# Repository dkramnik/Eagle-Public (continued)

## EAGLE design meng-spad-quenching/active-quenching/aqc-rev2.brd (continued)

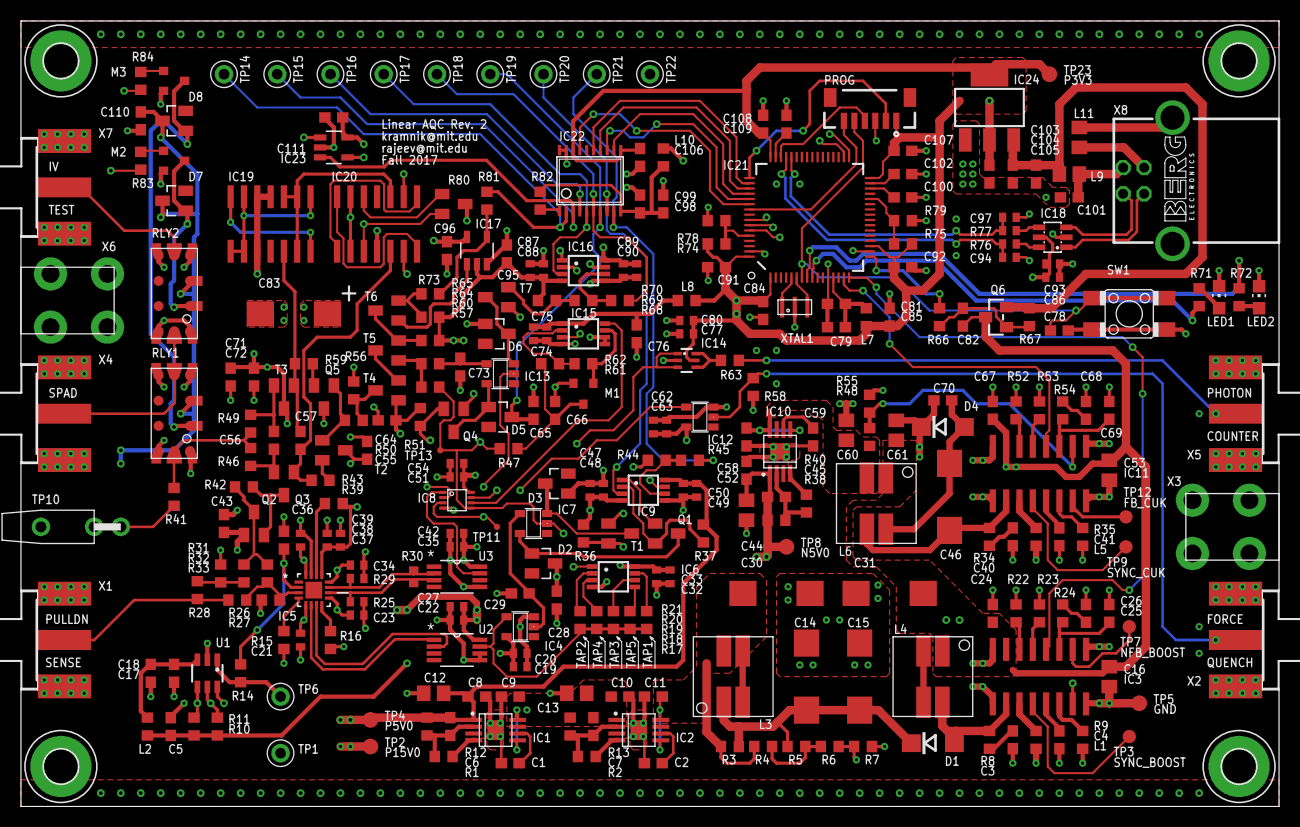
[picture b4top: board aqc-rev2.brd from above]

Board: 4 copper layers, 120.0 x 74.9 mm, 299 parts (0 on the bottom side), 171 nets.

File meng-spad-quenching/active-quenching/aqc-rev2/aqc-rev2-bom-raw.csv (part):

"Part";"Value";"Device";"Package";"Description";"";
"C1";"10n";"C-EUC0603";"C0603";"CAPACITOR, European symbol";"";
"C2";"10n";"C-EUC0603";"C0603";"CAPACITOR, European symbol";"";
"C3";"1n";"C-EUC0603";"C0603";"CAPACITOR, European symbol";"";
"C4";"1300p";"C-EUC0603";"C0603";"CAPACITOR, European symbol";"";
"C5";"100n";"C-EUC0603";"C0603";"CAPACITOR, European symbol";"";
"C6";"10n";"C-EUC0603";"C0603";"CAPACITOR, European symbol";"";
"C7";"10n";"C-EUC0603";"C0603";"CAPACITOR, European symbol";"";
"C8";"100n";"C-EUC0603";"C0603";"CAPACITOR, European symbol";"";
"C9";"100n";"C-EUC0603";"C0603";"CAPACITOR, European symbol";"";
"C10";"100n";"C-EUC0603";"C0603";"CAPACITOR, European symbol";"";
"C11";"100n";"C-EUC0603";"C0603";"CAPACITOR, European symbol";"";
"C12";"10u";"C-EUC0805";"C0805";"CAPACITOR, European symbol";"";
"C13";"10u";"C-EUC0805";"C0805";"CAPACITOR, European symbol";"";
"C14";"47u, 20V";"CPOL-EUCT7343";"CT7343";"POLARIZED CAPACITOR, European symbol";"";
"C15";"47u, 20V";"CPOL-EUCT7343";"CT7343";"POLARIZED CAPACITOR, European symbol";"";
"C16";"4.7u";"C-EUC0805";"C0805";"CAPACITOR, European symbol";"";
"C17";"4u7";"C-EUC0603";"C0603";"CAPACITOR, European symbol";"";
"C18";"100n";"C-EUC0603";"C0603";"CAPACITOR, European symbol";"";
"C19";"100n";"C-EUC0402";"C0402";"CAPACITOR, European symbol";"";
"C20";"10n";"C-EUC0402";"C0402";"CAPACITOR, European symbol";"";
"C21";"10n";"C-EUC0402";"C0402";"CAPACITOR, European symbol";"";
"C22";"10n";"C-EUC0402";"C0402";"CAPACITOR, European symbol";"";
"C23";"10n";"C-EUC0402";"C0402";"CAPACITOR, European symbol";"";
"C24";"100n";"C-EUC0603";"C0603";"CAPACITOR, European symbol";"";
"C25";"15n";"C-EUC0603";"C0603";"CAPACITOR, European symbol";"";
"C26";"220p";"C-EUC0603";"C0603";"CAPACITOR, European symbol";"";
"C27";"100n";"C-EUC0402";"C0402";"CAPACITOR, European symbol";"";
"C28";"470p";"C-EUC0603";"C0603";"CAPACITOR, European symbol";"";
"C29";"10p";"C-EUC0603";"C0603";"CAPACITOR, European symbol";"";
"C30";"47u, 20V";"CPOL-EUCT7343";"CT7343";"POLARIZED CAPACITOR, European symbol";"";
"C31";"47u, 20V";"CPOL-EUCT7343";"CT7343";"POLARIZED CAPACITOR, European symbol";"";
"C32";"100n";"C-EUC0402";"C0402";"CAPACITOR, European symbol";"";
"C33";"10n";"C-EUC0402";"C0402";"CAPACITOR, European symbol";"";
"C34";"100n";"C-EUC0402";"C0402";"CAPACITOR, European symbol";"";
"C35";"100n";"C-EUC0402";"C0402";"CAPACITOR, European symbol";"";
"C36";"1n";"C-EUC0603";"C0603";"CAPACITOR, European symbol";"";
"C37";"100n";"C-EUC0402";"C0402";"CAPACITOR, European symbol";"";
"C38";"100n";"C-EUC0402";"C0402";"CAPACITOR, European symbol";"";
"C39";"10n";"C-EUC0402";"C0402";"CAPACITOR, European symbol";"";
"C40";"10n";"C-EUC0603";"C0603";"CAPACITOR, European symbol";"";
"C41";"1300p";"C-EUC0603";"C0603";"CAPACITOR, European symbol";"";
"C42";"10n";"C-EUC0402";"C0402";"CAPACITOR, European symbol";"";
"C43";"100n";"C-EUC0603";"C0603";"CAPACITOR, European symbol";"";
"C44";"10u";"C-EUC0805";"C0805";"CAPACITOR, European symbol";"";
"C45";"10n";"C-EUC0603";"C0603";"CAPACITOR, European symbol";"";
"C46";"68u, 16V";"CPOL-EUCT7343";"CT7343";"POLARIZED CAPACITOR, European symbol";"";
"C47";"10n";"C-EUC0402";"C0402";"CAPACITOR, European symbol";"";
"C48";"100n";"C-EUC0402";"C0402";"CAPACITOR, European symbol";"";
"C49";"10n";"C-EUC0402";"C0402";"CAPACITOR, European symbol";"";
"C50";"100n";"C-EUC0402";"C0402";"CAPACITOR, European symbol";"";
"C51";"10n";"C-EUC0402";"C0402";"CAPACITOR, European symbol";"";
"C52";"100n";"C-EUC0603";"C0603";"CAPACITOR, European symbol";"";
"C53";"4.7u";"C-EUC0805";"C0805";"CAPACITOR, European symbol";"";
"C54";"100n";"C-EUC0402";"C0402";"CAPACITOR, European symbol";"";
"C55";"100n";"C-EUC0603";"C0603";"CAPACITOR, European symbol";"";
"C56";"10n";"C-EUC0603";"C0603";"CAPACITOR, European symbol";"";
"C57";"10n";"C-EUC0603";"C0603";"CAPACITOR, European symbol";"";
"C58";"100n";"C-EUC0603";"C0603";"CAPACITOR, European symbol";"";
"C59";"10n";"C-EUC0603";"C0603";"CAPACITOR, European symbol";"";
"C60";"10u, 10V";"C-EUC0805";"C0805";"CAPACITOR, European symbol";"";
"C61";"4.7u";"C-EUC0805";"C0805";"CAPACITOR, European symbol";"";
"C62";"10n";"C-EUC0402";"C0402";"CAPACITOR, European symbol";"";
"C63";"100n";"C-EUC0402";"C0402";"CAPACITOR, European symbol";"";
"C64";"100n";"C-EUC0603";"C0603";"CAPACITOR, European symbol";"";
"C65";"470p";"C-EUC0603";"C0603";"CAPACITOR, European symbol";"";
"C66";"1n";"C-EUC0603";"C0603";"CAPACITOR, European symbol";"";
"C67";"100n";"C-EUC0603";"C0603";"CAPACITOR, European symbol";"";
"C68";"33n\";"C-EUC0603";"C0603";"CAPACITOR, European symbol";"";
"C69";"DNP";"C-EUC0603";"C0603";"CAPACITOR, European symbol";"";
"C70";"DNP";"C-EUC0603";"C0603";"CAPACITOR, European symbol";"";
"C71";"100n";"C-EUC0603";"C0603";"CAPACITOR, European symbol";"";
"C72";"10n";"C-EUC0603";"C0603";"CAPACITOR, European symbol";"";
"C73";"10p";"C-EUC0603";"C0603";"CAPACITOR, European symbol";"";
"C74";"10n";"C-EUC0402";"C0402";"CAPACITOR, European symbol";"";
"C75";"100n";"C-EUC0402";"C0402";"CAPACITOR, European symbol";"";
"C76";"4u7";"C-EUC0603";"C0603";"CAPACITOR, European symbol";"";
"C77";"10n";"C-EUC0402";"C0402";"CAPACITOR, European symbol";"";
"C78";"10n";"C-EUC0603";"C0603";"CAPACITOR, European symbol";"";
"C79";"4u7";"C-EUC0603";"C0603";"CAPACITOR, European symbol";"";
"C80";"100n";"C-EUC0402";"C0402";"CAPACITOR, European symbol";"";
"C81";"4.7u";"C-EUC0603";"C0603";"CAPACITOR, European symbol";"";
"C82";"100n";"C-EUC0603";"C0603";"CAPACITOR, European symbol";"";
"C83";"47u, 20V";"CPOL-EUCT7343";"CT7343";"POLARIZED CAPACITOR, European symbol";"";
"C84";"100n";"C-EUC0603";"C0603";"CAPACITOR, European symbol";"";
"C85";"100n";"C-EUC0603";"C0603";"CAPACITOR, European symbol";"";
"C86";"100n";"C-EUC0402";"C0402";"CAPACITOR, European symbol";"";
"C87";"100n";"C-EUC0402";"C0402";"CAPACITOR, European symbol";"";
"C88";"10n";"C-EUC0402";"C0402";"CAPACITOR, European symbol";"";
"C89";"100n";"C-EUC0402";"C0402";"CAPACITOR, European symbol";"";
"C90";"10n";"C-EUC0402";"C0402";"CAPACITOR, European symbol";"";
"C91";"100n";"C-EUC0603";"C0603";"CAPACITOR, European symbol";"";
"C92";"100n";"C-EUC0603";"C0603";"CAPACITOR, European symbol";"";
"C93";"10n";"C-EUC0402";"C0402";"CAPACITOR, European symbol";"";
"C94";"47p";"C-EUC0402";"C0402";"CAPACITOR, European symbol";"";
"C95";"100n";"C-EUC0603";"C0603";"CAPACITOR, European symbol";"";
"C96";"100n";"C-EUC0603";"C0603";"CAPACITOR, European symbol";"";
"C97";"47p";"C-EUC0402";"C0402";"CAPACITOR, European symbol";"";
"C98";"100n";"C-EUC0603";"C0603";"CAPACITOR, European symbol";"";
"C99";"4u7";"C-EUC0603";"C0603";"CAPACITOR, European symbol";"";
"C100";"100n";"C-EUC0603";"C0603";"CAPACITOR, European symbol";"";
"C101";"10n";"C-EUC0603";"C0603";"CAPACITOR, European symbol";"";
"C102";"100n";"C-EUC0603";"C0603";"CAPACITOR, European symbol";"";
"C103";"100n";"C-EUC0603";"C0603";"CAPACITOR, European symbol";"";
"C104";"100n";"C-EUC0603";"C0603";"CAPACITOR, European symbol";"";
"C105";"4u7";"C-EUC0603";"C0603";"CAPACITOR, European symbol";"";
"C106";"100n";"C-EUC0603";"C0603";"CAPACITOR, European symbol";"";
"C107";"100n";"C-EUC0603";"C0603";"CAPACITOR, European symbol";"";
"C108";"100n";"C-EUC0603";"C0603";"CAPACITOR, European symbol";"";
"C109";"100n";"C-EUC0603";"C0603";"CAPACITOR, European symbol";"";
"C110";"100n";"C-EUC0603";"C0603";"CAPACITOR, European symbol";"";
"C111";"100n";"C-EUC0603";"C0603";"CAPACITOR, European symbol";"";
"D1";"CDBA140SL-HF";"DIODE-DO214AC";"DO214AC";"DIODE";"";
"D2";"BAS40";"BAS40";"SOT23";"Silicon Schottky Diodes";"";
"D3";"BAS40";"BAS40";"SOT23";"Silicon Schottky Diodes";"";
"D4";"CDBA140SL-HF";"DIODE-DO214AC";"DO214AC";"DIODE";"";
"D5";"BAS40";"BAS40";"SOT23";"Silicon Schottky Diodes";"";
"D6";"BAS40";"BAS40";"SOT23";"Silicon Schottky Diodes";"";
"D7";"BAS40";"BAS40";"SOT23";"Silicon Schottky Diodes";"";
"D8";"BAS40";"BAS40";"SOT23";"Silicon Schottky Diodes";"";
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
